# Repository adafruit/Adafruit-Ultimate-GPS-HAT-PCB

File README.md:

## Adafruit Ultimate GPS HAT PCB

<a href="http://www.adafruit.com/products/2324"><br/>
Click here to purchase one from the Adafruit shop
</a>

PCB files for the Adafruit Ultimate GPS HAT. Format is EagleCAD schematic and board layout
- http://www.adafruit.com/product/2324

This new HAT from Adafruit adds our celebrated Ultimate GPS on it, so you can add precision time and location to your Raspberry Pi Model Pi 3, Pi Zero, A+, B+, or Pi 2 & 3

Here's the low-down on the GPS module:

-165 dBm sensitivity, 10 Hz updates, 66 channels
Only 20mA current draw
Built in Real Time Clock (RTC) - slot in a CR1220 backup battery for 7-years or more of timekeeping even if the Raspberry Pi is off!
PPS output on fix, by default connected to pin #4
Internal patch antenna which works quite well when used outdoors + u.FL connector for external active antenna for when used indoors or in locations without a clear sky view
Fix status LED blinks to let you know when the GPS has determined the current coordinates
We spun up a HAT based on our Ultimate GPS, added a coin-cell holder for RTC usage, break-outs for all the Raspberry Pi's extra pins, and plenty of prototyping area for adding LEDs, sensors, and more.

Please note, this HAT takes over the Raspberry Pi's hardware UART to send/receive data to and from the GPS module. So, if you need to use the RX/TX pins with a console cable, you cannot also use this HAT. Instead, you'll have to use a composite or HDMI monitor and keyboard to log in, or use ssh to connect over the network to your Pi. Read up on our tutorial for more information on how to use this fine HAT

Comes as a fully assembled GPS + PCB and an additional 2x20 GPIO header. Some light soldering is required to attach the 2x20 GPIO header to the HAT but it's fast and easy for anyone with a soldering iron and solder. You can also swap the plain female header we have with a 'stacky' type that lets you plug in a hat or GPIO cable on top or a slim ultra-low-profile header.

To make air-shipping eaiser, this HAT does not come with a 12mm coin battery! 

### License

Adafruit invests time and resources providing this open source design, please support Adafruit and open-source hardware by purchasing products from [Adafruit.com](https://www.adafruit.com)!

Creative Commons Attribution, Share-Alike license, check license.txt for more information All text above must be included in any redistribution - 
See license.txt for more information.

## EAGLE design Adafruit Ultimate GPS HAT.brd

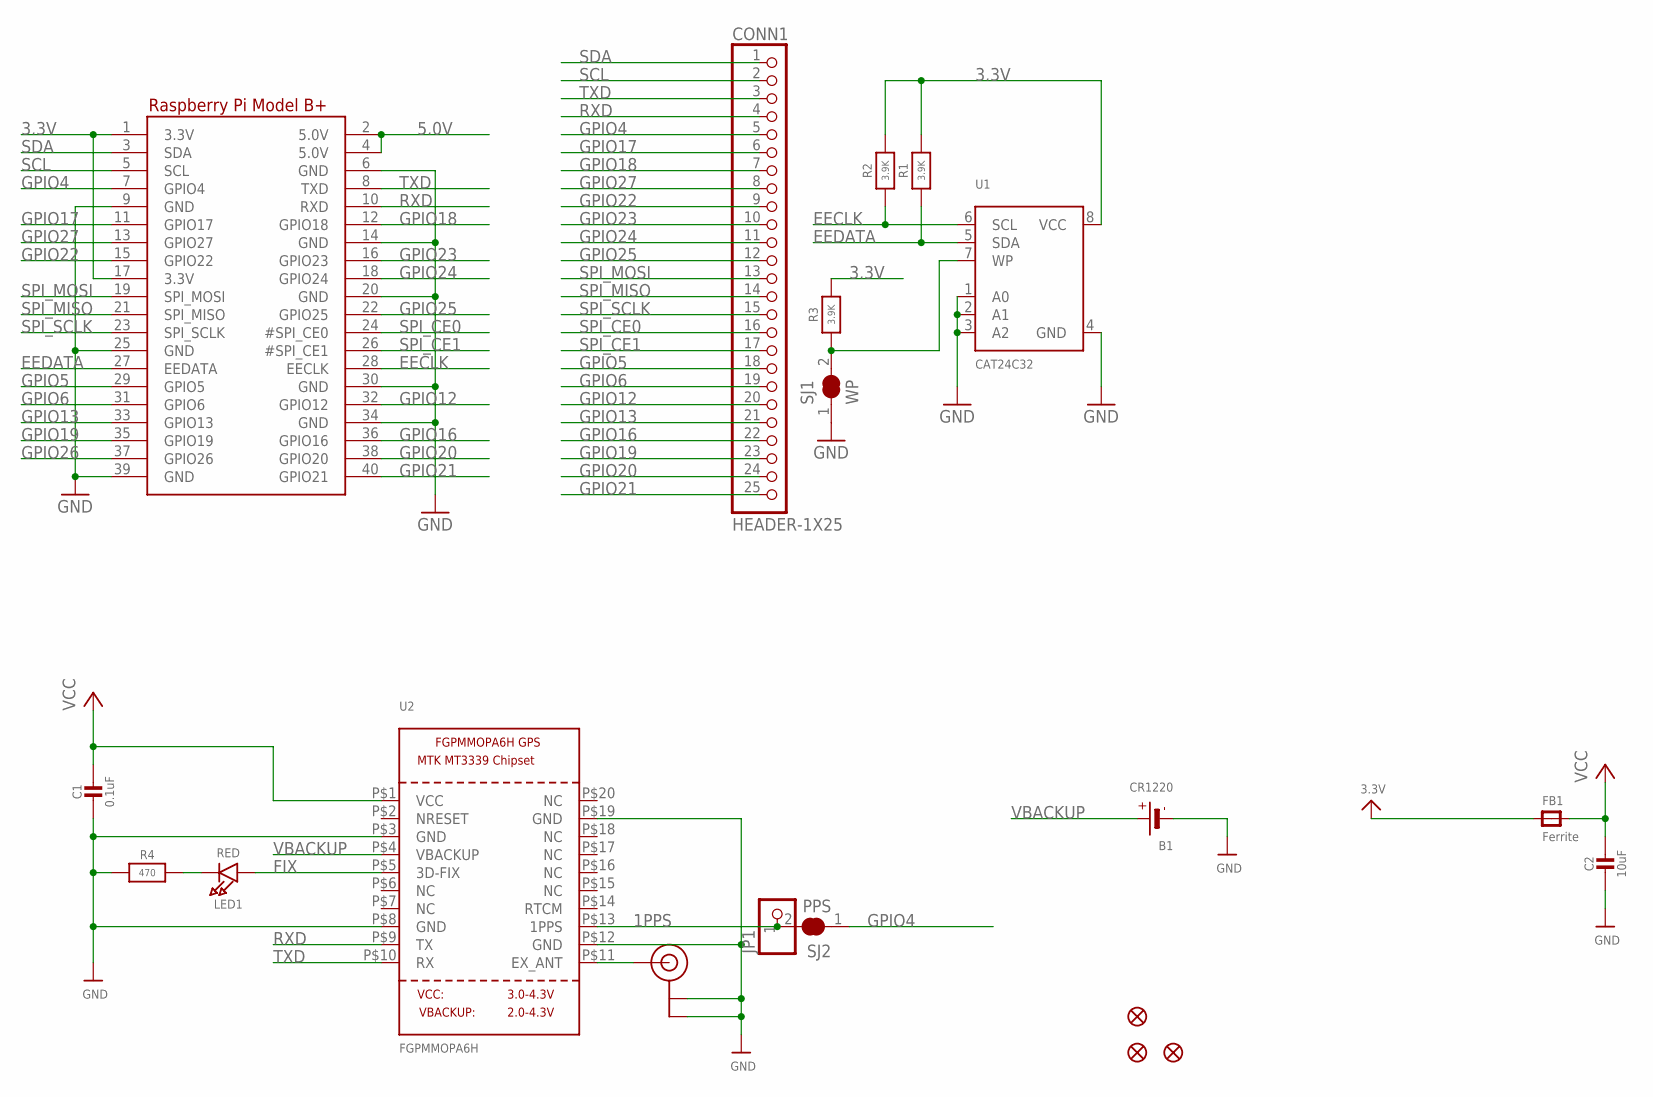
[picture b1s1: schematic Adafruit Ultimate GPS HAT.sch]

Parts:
B1: CR1220
C1: 0.1uF; 0805-NO
C2: 10uF; 0805-NO
CONN1: HEADER-1X25; 1X25_ROUND_70MIL
FB1: Ferrite; 0805
FID1, FID2, FID3: FIDUCIAL""; FIDUCIAL_1MM
JP1: PINHD-1X1CB; 1X01-CLEANBIG
LED1: RED; CHIPLED_0805
R1, R2, R3: 3.9K; 0805-NO
R4: 470; 0805-NO
RPI1: RASPBERRYPI_BPLUS_HATSLOTS; PI_HAT_SLOTS
SJ1: WP; SOLDERJUMPER_CLOSEDWIRE
SJ2: PPS; SOLDERJUMPER_CLOSEDWIRE
U1: CAT24C32; SOIC8_150MIL
U2: FGPMMOPA6H
U$20: U.FL

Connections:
1PPS: JP1.1, SJ2.2, U2.P$13 (1PPS)
3.3V: FB1.1, R1.2, R2.2, R3.2, RPI1.1 (3.3V), RPI1.17 (3.3V), U1.8 (VCC)
5.0V: RPI1.2 (5.0V), RPI1.4 (5.0V)
EECLK: R2.1, RPI1.28 (EECLK), U1.6 (SCL)
EEDATA: R1.1, RPI1.27 (EEDATA), U1.5 (SDA)
FIX: LED1.A, U2.P$5 (3D-FIX)
GND: B1.-, C1.2, C2.2, R4.1, RPI1.6 (GND), RPI1.9 (GND), RPI1.14 (GND), RPI1.20 (GND), RPI1.25 (GND), RPI1.30 (GND), RPI1.34 (GND), RPI1.39 (GND), SJ1.1, U1.1 (A0), U1.2 (A1), U1.3 (A2), U1.4 (GND), U2.P$3 (GND), U2.P$8 (GND), U2.P$12 (GND), U2.P$19 (GND), U$20.P$1 (GND), U$20.P$2 (GND)
GPIO4: CONN1.5, RPI1.7 (GPIO4), SJ2.1
GPIO5: CONN1.18, RPI1.29 (GPIO5)
GPIO6: CONN1.19, RPI1.31 (GPIO6)
GPIO12: CONN1.20, RPI1.32 (GPIO12)
GPIO13: CONN1.21, RPI1.33 (GPIO13)
GPIO16: CONN1.22, RPI1.36 (GPIO16)
GPIO17: CONN1.6, RPI1.11 (GPIO17)
GPIO18: CONN1.7, RPI1.12 (GPIO18)
GPIO19: CONN1.23, RPI1.35 (GPIO19)
GPIO20: CONN1.24, RPI1.38 (GPIO20)
GPIO21: CONN1.25, RPI1.40 (GPIO21)
GPIO22: CONN1.9, RPI1.15 (GPIO22)
GPIO23: CONN1.10, RPI1.16 (GPIO23)
GPIO24: CONN1.11, RPI1.18 (GPIO24)
GPIO25: CONN1.12, RPI1.22 (GPIO25)
GPIO26: RPI1.37 (GPIO26)
GPIO27: CONN1.8, RPI1.13 (GPIO27)
unnamed: R3.1, SJ1.2, U1.7 (WP)
unnamed: LED1.C, R4.2
unnamed: U2.P$11 (EX_ANT), U$20.P$3 (SIGNAL)
RXD: CONN1.4, RPI1.10 (RXD), U2.P$9 (TX)
SCL: CONN1.2, RPI1.5 (SCL)
SDA: CONN1.1, RPI1.3 (SDA)
SPI_CE0: CONN1.16, RPI1.24 (#SPI_CE0)
SPI_CE1: CONN1.17, RPI1.26 (#SPI_CE1)
SPI_MISO: CONN1.14, RPI1.21 (SPI_MISO)
SPI_MOSI: CONN1.13, RPI1.19 (SPI_MOSI)
SPI_SCLK: CONN1.15, RPI1.23 (SPI_SCLK)
TXD: CONN1.3, RPI1.8 (TXD), U2.P$10 (RX)
VBACKUP: B1.+$1 (+), U2.P$4 (VBACKUP)
VCC: C1.1, C2.1, FB1.2, U2.P$1 (VCC)

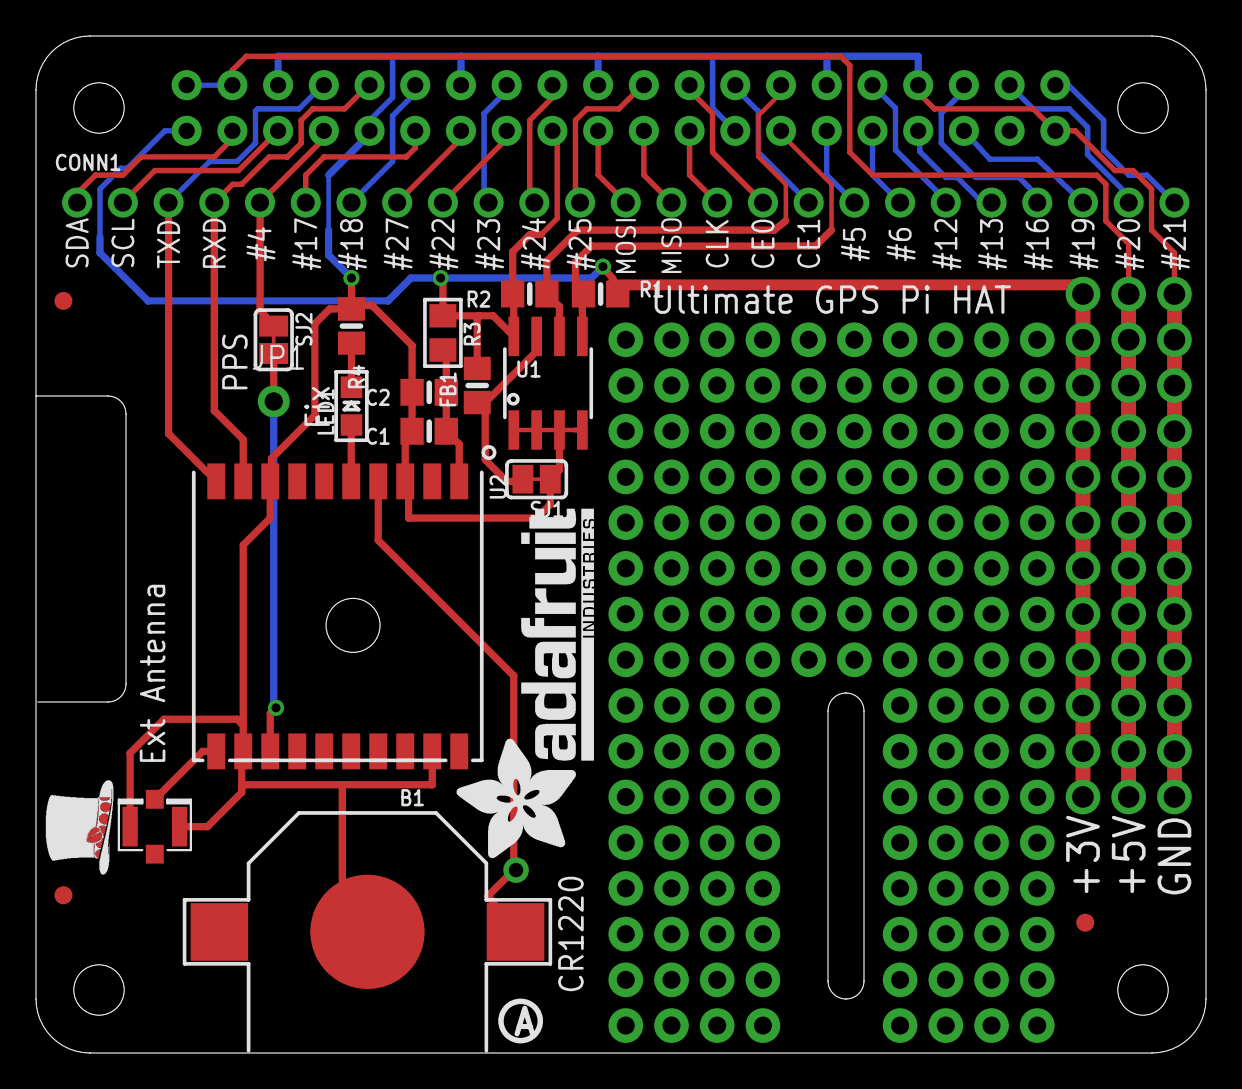
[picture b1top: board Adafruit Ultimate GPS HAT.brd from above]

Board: 2 copper layers, 65.0 x 56.5 mm, 23 parts (0 on the bottom side), 37 nets.

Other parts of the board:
U$3: ADAFRUIT_TEXT_20MM
U$4: PIHATLOGO
U$6: PCBFEAT-REV-056

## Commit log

2016-10-06 init

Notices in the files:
parts and their libraries:
microbuilder: This work is placed in the public domain, and may be freely used for commercial and non-commercial work with the following conditions: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
